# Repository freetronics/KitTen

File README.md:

Freetronics KitTen
==================
Copyright 2010-2013 Freetronics Pty Ltd  
Freetronics site:  www.freetronics.com  
Freetronics email: info@freetronics.com  

A fully-featured Arduino-compatible board in kit form. Includes a
voltage regulator and extensive filtering, plus a prototyping area.

Features:

 * Prototyping area
 * Overlay guide where you need it (both top and bottom)
 * D13 pin works for everything thanks to FET isolation
 * RX pin biased
 * Mounting holes and power pads
 * R3 (revision 3) Arduino header format

More information is available at:

  http://www.freetronics.com/kitten

INSTALLATION
------------
The design is saved as an EAGLE project. EAGLE PCB design software is
available from www.cadsoftusa.com free for non-commercial use. To use
this project download it and place the directory containing these files
into the "eagle" directory on your computer. Then open EAGLE and
navigate to Projects -> eagle -> KitTen.

DISTRIBUTION
------------
The specific terms of distribution of this project are governed by the
license referenced below.

LICENSE
-------
This work is licensed under the
Creative Commons Attribution-Share Alike License.  
To view a copy of this license, visit

  http://creativecommons.org/licenses/by-sa/3.0/  
  http://creativecommons.org/licenses/by-sa/3.0/legalcode

or send a letter to

  Creative Commons  
  171 Second Street, Suite 300  
  San Francisco  
  California, 94105  
  USA

The "license" folder within this repository also contains copies of the
licences referenced above.

CREDITS
-------
The KitTen was designed by Jonathan Oxer (jon@freetronics.com) and Marc
Alexander (marc@freetronics.com) based on previous work by the Arduino
team and various Freeduino variants including the Diavolino.

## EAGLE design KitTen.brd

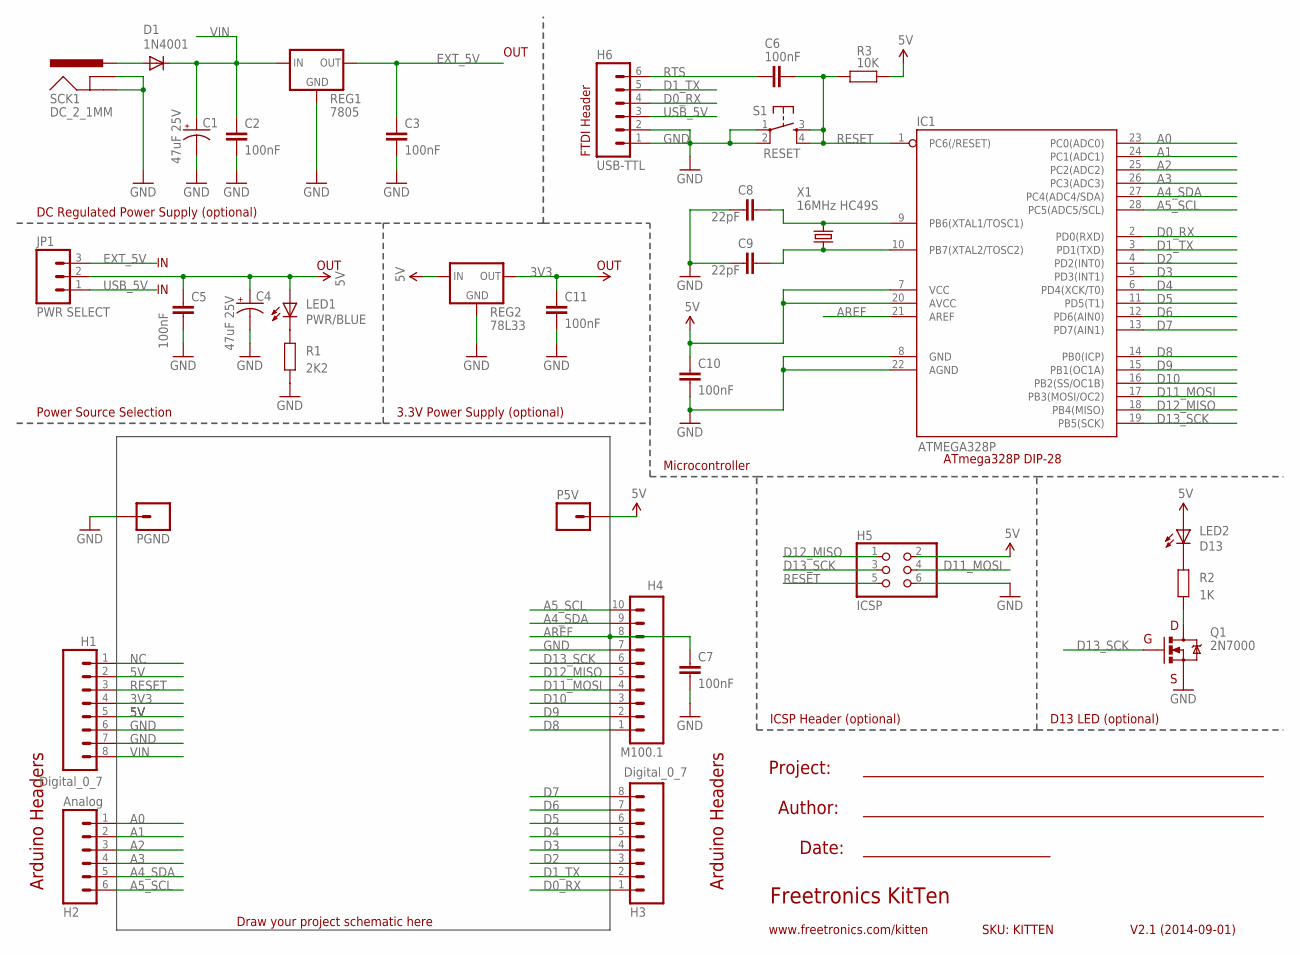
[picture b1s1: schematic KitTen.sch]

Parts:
C1, C4: 47uF 25V; CPOL-RADIAL-10UF-25V
C2, C3, C5, C6, C7, C10, C11: 100nF; CAP-PTH-SMALL
C8, C9: 22pF; CAP-PTH-SMALL
D1: 1N4001; DIODE-1N4001
H1, H3: Digital_0_7; 1X08
H2: Analog; 1X06
H4: M100.1; 1X10
H5: ICSP; 2X03
H6: USB-TTL; 1X06
IC1: ATMEGA328P; DIL28-3
JP1: PWR SELECT; 1X03
LED1: PWR/BLUE; LED3MM
LED2: D13; LED3MM
P5V: M01SMD; LUXEON-PAD
PGND: M01SMD; LUXEON-PAD
Q1: 2N7000; TO92
R1: 2K2; AXIAL-0.3
R2: 1K; AXIAL-0.3
R3: 10K; AXIAL-0.3
REG1: 7805; 78XXL
REG2: 78L33; TO92
S1: RESET; TACTILE-PTH
SCK1: DC_2_1MM; POWER_JACK_PTH
X1: 16MHz HC49S; HC49U-V

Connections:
3V3: C11.1, H1.4, REG2.1 (OUT)
5V: C4.1 (+), C5.1, C10.1, H1.2, H1.5, H5.2, IC1.7 (VCC), IC1.20 (AVCC), JP1.2, LED1.A, LED2.A, P5V.P$1, R3.P$2 (2), REG2.3 (IN)
A0: H2.1, IC1.23 (PC0(ADC0))
A1: H2.2, IC1.24 (PC1(ADC1))
A2: H2.3, IC1.25 (PC2(ADC2))
A3: H2.4, IC1.26 (PC3(ADC3))
A4_SDA: H2.5, H4.9, IC1.27 (PC4(ADC4/SDA))
A5_SCL: H2.6, H4.10, IC1.28 (PC5(ADC5/SCL))
AREF: C7.1, H4.8, IC1.21 (AREF)
D0_RX: H3.1, H6.4, IC1.2 (PD0(RXD))
D1_TX: H3.2, H6.5, IC1.3 (PD1(TXD))
D2: H3.3, IC1.4 (PD2(INT0))
D3: H3.4, IC1.5 (PD3(INT1))
D4: H3.5, IC1.6 (PD4(XCK/T0))
D5: H3.6, IC1.11 (PD5(T1))
D6: H3.7, IC1.12 (PD6(AIN0))
D7: H3.8, IC1.13 (PD7(AIN1))
D8: H4.1, IC1.14 (PB0(ICP))
D9: H4.2, IC1.15 (PB1(OC1A))
D10: H4.3, IC1.16 (PB2(SS/OC1B))
D11_MOSI: H4.4, H5.4, IC1.17 (PB3(MOSI/OC2))
D12_MISO: H4.5, H5.1, IC1.18 (PB4(MISO))
D13_SCK: H4.6, H5.3, IC1.19 (PB5(SCK)), Q1.2 (G)
EXT_5V: C3.1, JP1.3, REG1.OUT
GND: C1.2 (-), C2.2, C3.2, C4.2 (-), C5.2, C7.2, C8.1, C9.1, C10.2, C11.2, H1.6, H1.7, H4.7, H5.6, H6.1, H6.2, IC1.8 (GND), IC1.22 (AGND), PGND.P$1, Q1.1 (S), R1.P$1 (1), REG1.GND, REG2.2 (GND), S1.1, S1.2, SCK1.GND, SCK1.GNDBREAK
unnamed: LED2.K (C), R2.P$2 (2)
unnamed: C8.2, IC1.9 (PB6(XTAL1/TOSC1)), X1.2
unnamed: Q1.3 (D), R2.P$1 (1)
unnamed: C9.2, IC1.10 (PB7(XTAL2/TOSC2)), X1.1
unnamed: D1.A, SCK1.PWR
unnamed: LED1.K (C), R1.P$2 (2)
NC: H1.1
RESET: C6.2, H1.3, H5.5, IC1.1 (PC6(/RESET)), R3.P$1 (1), S1.3, S1.4
RTS: C6.1, H6.6
USB_5V: H6.3, JP1.1
VIN: C1.1 (+), C2.1, D1.C, H1.8, REG1.IN

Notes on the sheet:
Draw your project schematic here
Freetronics KitTen
V2.1 (2014-09-01)
SKU: KITTEN
www.freetronics.com/kitten
DC Regulated Power Supply (optional)
ATmega328P DIP-28
Power Source Selection
3.3V Power Supply (optional)
Arduino Headers
Project:
Date:
ICSP Header (optional)
D13 LED (optional)
Microcontroller
OUT
FTDI Header
Author:

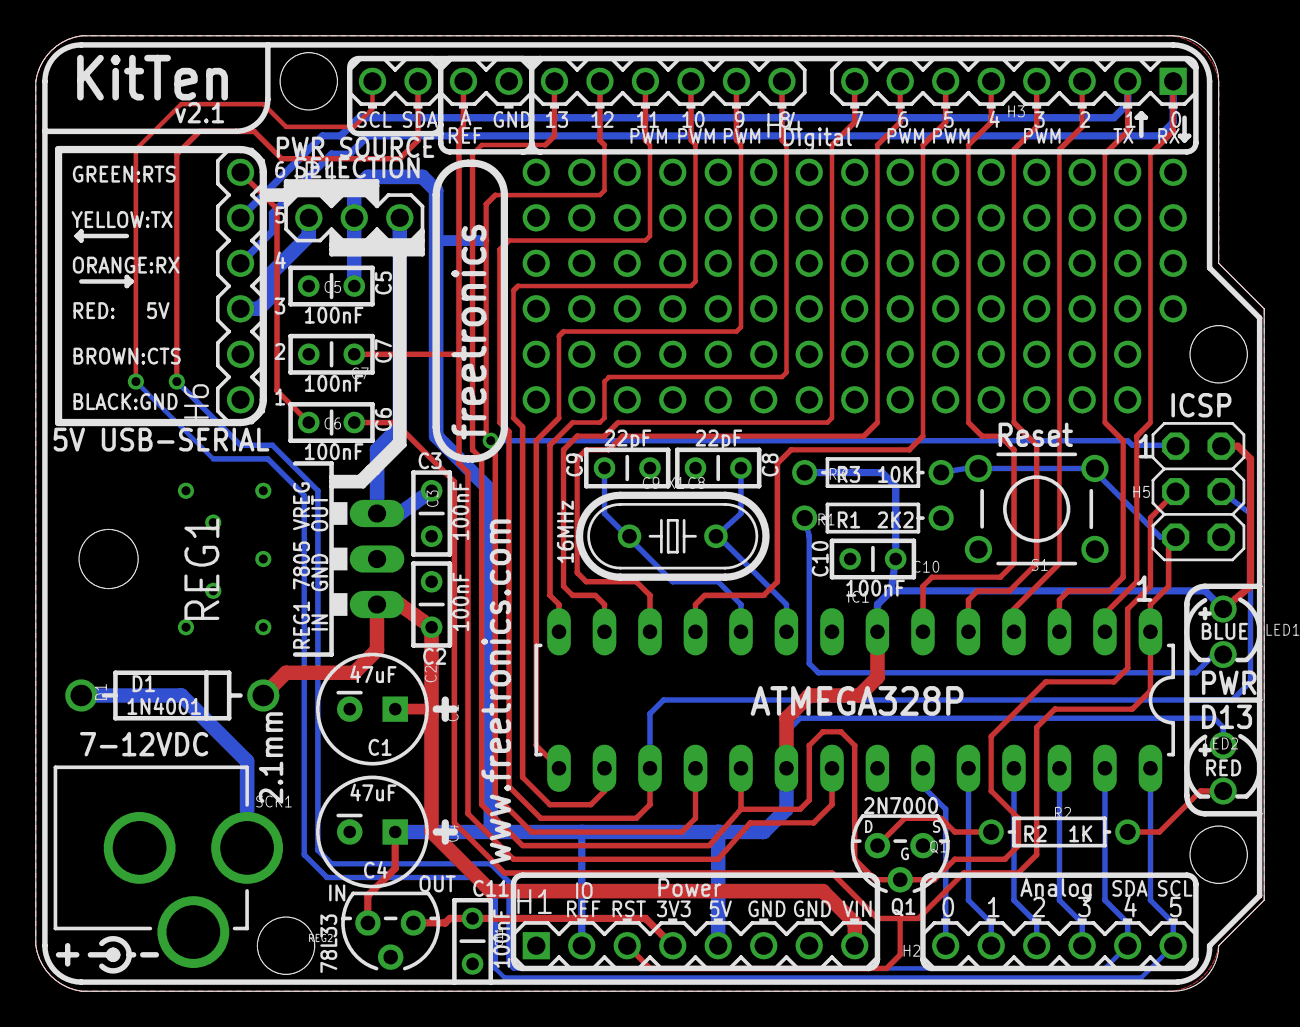
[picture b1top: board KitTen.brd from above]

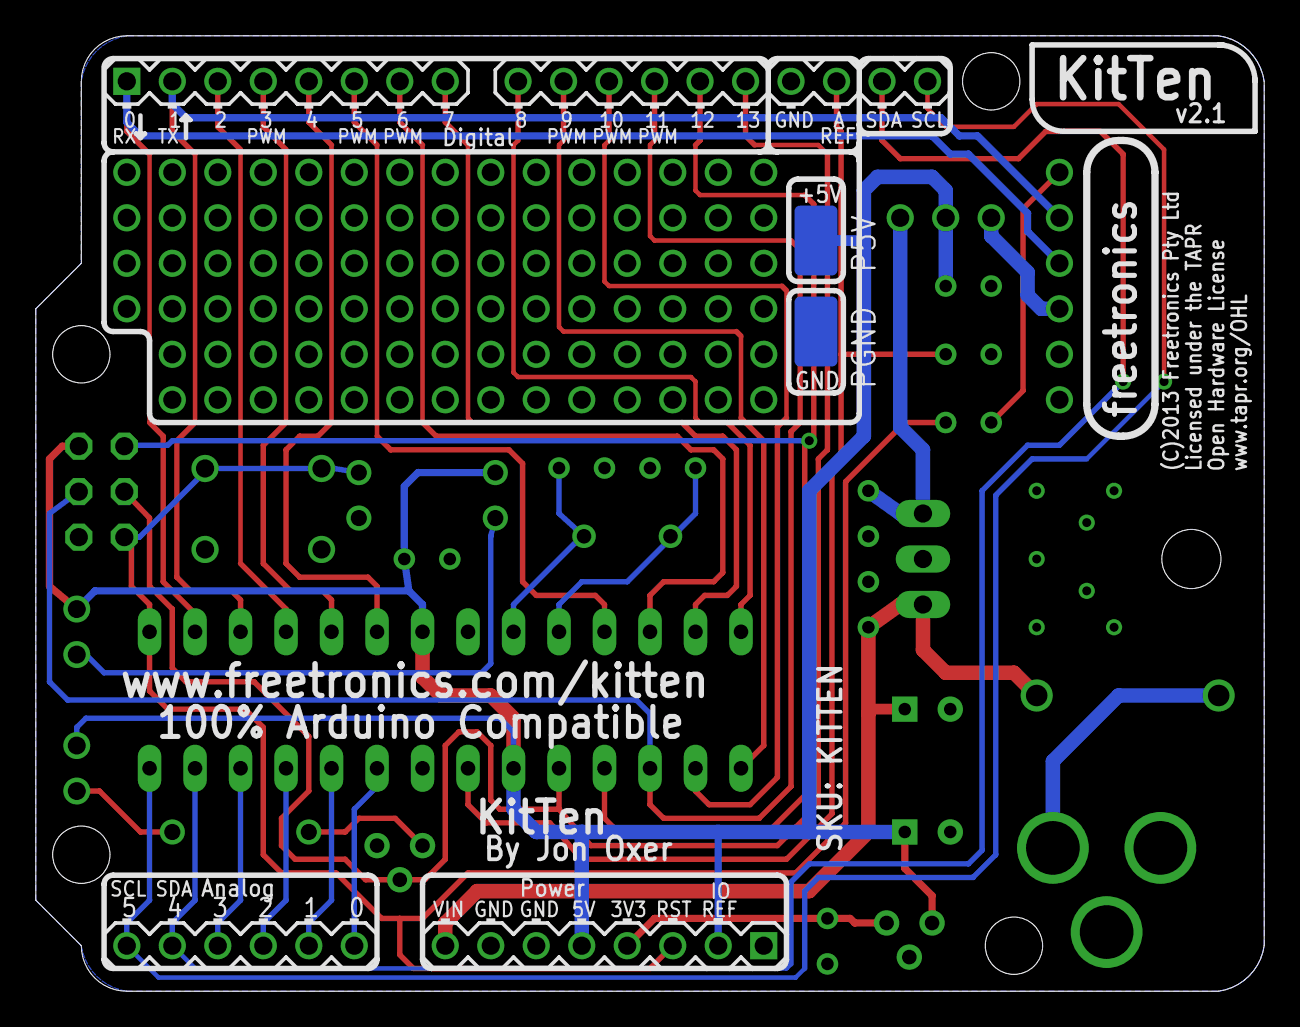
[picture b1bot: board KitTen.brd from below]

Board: 2 copper layers, 68.6 x 53.3 mm, 33 parts (2 on the bottom side), 35 nets.

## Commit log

2010-09-01 Initial import of rough project concept
2010-09-02 More SMT parts replacement and schematic rearrangement
2010-09-02 Moving parts around to get a basic layout
2010-09-02 Moved parts around, trying to find a neat layout
2010-09-03 Routing getting close to finished, major elements in place
2010-09-03 Tweaking PCB layout
2010-09-04 Added 3.3V supply; major overhaul of schematic; reduced traces in proto area to 10thou
2010-09-07 Moved 3.3V reg onto the board, moved other things around
2010-09-07 Routing tweaks. Getting closer, but still ugly around the MOSFET in particular
2010-09-08 Routing tweaks and assembly overlay
2010-09-08 Fixed MOSFET pinout and added part IDs to overlay
2010-09-08 Fixed MOSFET part number
2010-09-08 Moved cap polarity indicators
2010-09-11 Made a big mess by moving stuff around
2010-09-26 Nearly final routing and overlay, still some cleanups to go
2010-09-28 Marc test push 1
2010-09-28 Removed 100K pulldown on RX, and moved 47uF to after power select jumper
2010-09-28 More positioning, routing, and overlay tweaks
2010-09-28 More routing cleanups. Hopefully final now
2010-09-29 Improved overlay and added thermal relief to voltage reg
2010-09-29 Made via positions under vreg neater
2010-09-29 Marc test push 2
2010-10-04 Tweak location of MOSFET to provide more space near header markings
2013-02-13 Updated to R3 header format
2014-09-01 Improved silkscreen for v1.0 release
2014-09-01 Improved silkscreen for v2.0 release
2016-06-06 Improved silkscreen, removed docs reference from README, bumped version for 2.1 release

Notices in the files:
KitTen.brd:
Licensed under the TAPR
Open Hardware License
(C)2013 Freetronics Pty Ltd
parts and their libraries:
freetronics-marc: Licensing: CC v3.0 Share-Alike You are welcome to use this library for commercial purposes.
